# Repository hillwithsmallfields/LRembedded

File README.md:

# LRembedded

Embedded controllers for my Land Rover

I rebuilt and stretched a Land Rover a few years ago, and am starting
to add some microcontrollers.

battery_monitor_charger
=======================

A raspberry pi based system in my garage, connected to the vehicle
batteries by an umbilical, that monitors the voltage and switches a
charger on as needed; also alerts me if the battery connection is lost.

central
=======

An ADK Mega that looks at lots of status lines and communicates with
an Android tablet.

heater
======

Controls some motorized valves directing the output of an air heater.

mc8_tester
==========

A tester for the 8-pin connection system I use for the main wiring,
with connection names built in.

tacho
=====

Scales the output frequency of the alternator tacho connection to
match the requirements of the gauge.

upperwinch
==========

Soft-start controller for a small electric winch.

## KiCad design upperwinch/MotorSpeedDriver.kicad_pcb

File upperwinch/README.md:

MotorSpeedDriver
================

This is an Arduino-based driver for a motor speed controller,
providing ramp-up and ramp-down of speed from two buttons instead of
having to operate switches and a potentiometer.

The motor is a small (900Kgf) winch on my Land Rover roof rack.

The circuit that this combination replaces is an H-bridge of relays
operated by pairs of pushbuttons (on different parts of the vehicle),
one of each pair to run it in each direction.

As the winch is noisy, I wanted to make it possible to vary the speed,
but I wanted to keep the simple two-button interface.

I asked an electronics professional about designing the motor
controller, and he said don't even try at that sort of current (70A),
just buy a ready-made one; too much can go wrong (like switching on
the wrong parts of an H-bridge together).  The unit I bought has a
potentiometer with three connections, and a click-switch on it with
two; and an SPDT switch for selecting the direction.  Both of the
switches are to ground, and work by pulling down.

Hardware
========

For experimentation, I'm using an Arduino Nano; for the final version,
on a PCB, I'll use an ATmega328 directly.

Software
========

Operation
---------

Pressing one button steadily increases the speed in that direction; if
the motor was going in the other direction, it'll slow it down, until
it passes through zero and speeds up in the other direction.

Pressing both buttons at once stops the motor immediately.

Starting
--------

As the buttons are exposed to the elements, although they're nominally
weatherproof, sometimes it takes a few presses to get them to close
the circuit, and as I don't want to risk starting the motor in one
direction then not being able to stop it, the software won't start the
motor until both buttons have been pressed and released.

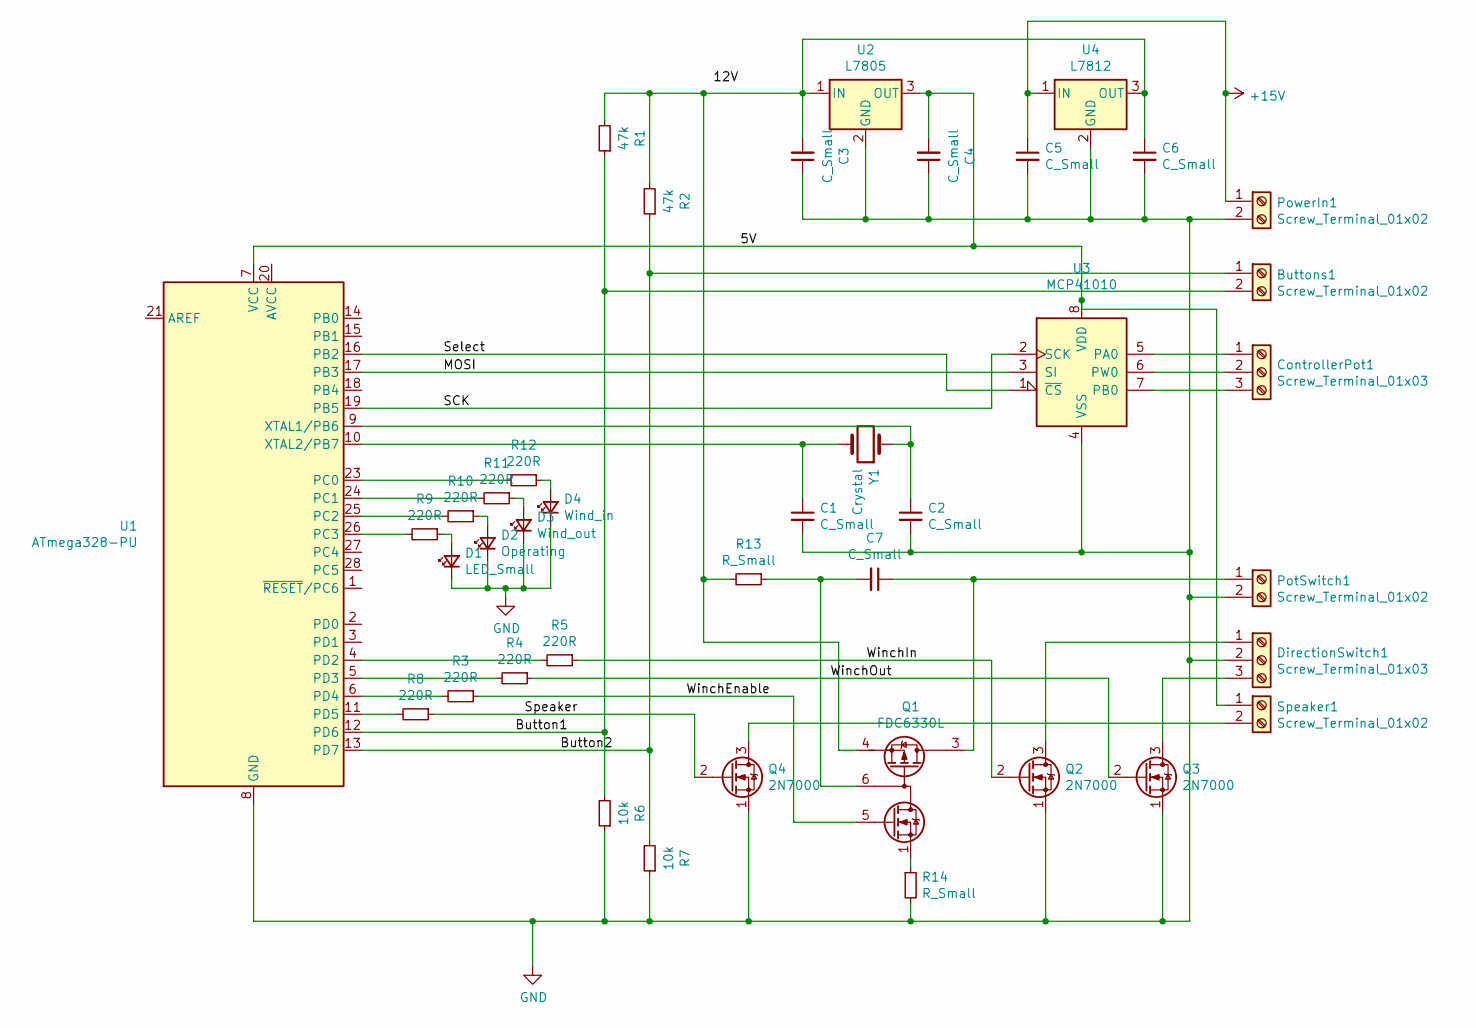
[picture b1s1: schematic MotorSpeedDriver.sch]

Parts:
Buttons1: Screw_Terminal_01x02; TerminalBlock_Phoenix_MKDS-3-2-5.08_1x02_P5.08mm_Horizontal
C1, C2, C3, C4, C5, C6, C7: C_Small; C_Disc_D12.0mm_W4.4mm_P7.75mm
ControllerPot1: Screw_Terminal_01x03; TerminalBlock_Phoenix_MKDS-3-3-5.08_1x03_P5.08mm_Horizontal
D1: LED_Small; LED_D5.0mm
D2: Operating; LED_D5.0mm
D3: Wind_out; LED_D5.0mm
D4: Wind_in; LED_D5.0mm
DirectionSwitch1: Screw_Terminal_01x03; TerminalBlock_Phoenix_MKDS-3-3-5.08_1x03_P5.08mm_Horizontal
PotSwitch1: Screw_Terminal_01x02; TerminalBlock_Phoenix_MKDS-3-2-5.08_1x02_P5.08mm_Horizontal
PowerIn1: Screw_Terminal_01x02; TerminalBlock_Phoenix_MKDS-3-2-5.08_1x02_P5.08mm_Horizontal
Q1: FDC6330L; TSOT-23-6_HandSoldering
Q2, Q3, Q4: 2N7000; TO-92_Inline
R1, R2: 47k; R_Axial_DIN0309_L9.0mm_D3.2mm_P12.70mm_Horizontal
R3, R4, R5, R8, R9, R10, R11, R12: 220R; R_Axial_DIN0309_L9.0mm_D3.2mm_P12.70mm_Horizontal
R6, R7: 10k; R_Axial_DIN0309_L9.0mm_D3.2mm_P12.70mm_Horizontal
R13, R14: R_Small; R_Axial_DIN0309_L9.0mm_D3.2mm_P12.70mm_Horizontal
Speaker1: Screw_Terminal_01x02; TerminalBlock_Phoenix_MKDS-3-2-5.08_1x02_P5.08mm_Horizontal
U1: ATmega328-PU; DIP-28_W7.62mm
U2: L7805; TO-220-3_Vertical
U3: MCP41010; DIP-8_W7.62mm
U4: L7812; TO-220-3_Vertical
Y1: Crystal; Crystal_HC18-U_Horizontal

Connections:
+15V: C5.1, PowerIn1.1, U4.1 (IN)
/5V: C4.2, Speaker1.1, U1.7 (VCC), U2.3 (OUT), U3.8 (VDD)
/Button1: Buttons1.2, R1.1, R6.2, U1.12 (PD6)
/Button2: Buttons1.1, R2.1, R7.2, U1.13 (PD7)
/MOSI: U1.17 (PB3), U3.3 (SI)
/SCK: U1.19 (PB5), U3.2 (SCK)
/Select: U1.16 (PB2), U3.1 (~CS)
/Speaker: Q4.2 (G), R8.1
/WinchEnable: Q1.5 (G1), R3.1
/WinchIn: Q2.2 (G), R5.1
/WinchOut: Q3.2 (G), R4.1
GND: C1.2, C2.2, C3.1, C4.1, C5.2, C6.2, D1.1 (K), D2.1 (K), D3.1 (K), D4.1 (K), DirectionSwitch1.2, PotSwitch1.2, PowerIn1.2, Q2.1 (S), Q3.1 (S), Q4.1 (S), R6.1, R7.1, R14.2, U1.8 (GND), U1.22 (GND), U2.2 (GND), U3.4 (VSS), U4.2 (GND)
unnamed: C1.1, U1.10 (XTAL2/PB7), Y1.2
unnamed: C2.1, U1.9 (XTAL1/PB6), Y1.1
unnamed: C3.2, C6.1, Q1.4 (S2), R1.2, R2.2, R13.2, U2.1 (IN), U4.3 (OUT)
unnamed: C7.1, PotSwitch1.1, Q1.2 (D2), Q1.3 (D2)
unnamed: C7.2, Q1.6 (D1), R13.1
unnamed: ControllerPot1.1, U3.5 (PA0)
unnamed: ControllerPot1.2, U3.6 (PW0)
unnamed: ControllerPot1.3, U3.7 (PB0)
unnamed: D1.2 (A), R9.1
unnamed: D2.2 (A), R10.1
unnamed: D3.2 (A), R11.1
unnamed: D4.2 (A), R12.1
unnamed: DirectionSwitch1.1, Q2.3 (D)
unnamed: DirectionSwitch1.3, Q3.3 (D)
unnamed: Q1.1 (S1), R14.1
unnamed: Q4.3 (D), Speaker1.2
unnamed: R3.2, U1.6 (PD4)
unnamed: R4.2, U1.5 (PD3)
unnamed: R5.2, U1.4 (PD2)
unnamed: R8.2, U1.11 (PD5)
unnamed: R9.2, U1.26 (PC3)
unnamed: R10.2, U1.25 (PC2)
unnamed: R11.2, U1.24 (PC1)
unnamed: R12.2, U1.23 (PC0)

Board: 2 copper layers, 40 parts (1 on the bottom side), 36 nets, no tracks yet.

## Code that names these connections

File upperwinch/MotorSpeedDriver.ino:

#include <SPI.h>

#define WITH_LEDs 1

const int ControllerInPin     = 2;  // PD2 // 4
const int ControllerOutPin    = 3;  // PD3 // 5
const int ControllerEnablePin = 4;  // PD4 // 6

const int SpeakerPin          = 5;  // PD5 // 11

const int ButtonInPin         = 6;  // PD6 // 12
const int ButtonOutPin        = 7;  // PD7 // 13

const int PotCSPin            = 10; // PB2 // 16
// MOSI                       = 11; // PB3 // 17
// MISO                       = 12; // PB4 // 18
// SCK                        = 13; // PB5 // 19

#ifdef WITH_LEDs
const int LedInPin            = A0; // PC0 // 23
const int LedOutPin           = A1; // PC1 // 24
const int LedOperatingPin     = A2; // PC2 // 25
const int LedStartingPin      = A3; // PC4 // 26
#endif

void setup() {
  pinMode(ButtonInPin, INPUT);
  pinMode(ButtonOutPin, INPUT);
  pinMode(PotCSPin, OUTPUT);
  pinMode(ControllerInPin, OUTPUT);
  pinMode(ControllerOutPin, OUTPUT);
  pinMode(ControllerEnablePin, OUTPUT);
  pinMode(SpeakerPin, OUTPUT);
#ifdef WITH_LEDs
  pinMode(LedInPin, OUTPUT);
  pinMode(LedOutPin, OUTPUT);
  pinMode(LedOperatingPin, OUTPUT);
  pinMode(LedStartingPin, OUTPUT);
#endif
  // initialize SPI:
  SPI.begin(); 
#ifdef WITH_LEDs
  digitalWrite(LedStartingPin, HIGH);
  digitalWrite(LedOperatingPin, LOW);
  digitalWrite(LedInPin, LOW);
  digitalWrite(LedOutPin, LOW);
#endif
}

void set_pot(int setting) {
  digitalWrite(PotCSPin, LOW);
  delay(100);
  SPI.transfer(setting);
  delay(100);
  digitalWrite(PotCSPin, HIGH);
}

void set_speed(int speed) {
  if (speed == 0) {
    digitalWrite(ControllerEnablePin, LOW);
    digitalWrite(ControllerInPin, LOW);
    digitalWrite(ControllerOutPin, LOW);
    set_pot(0);
#ifdef WITH_LEDs
    digitalWrite(LedInPin, LOW);
    digitalWrite(LedOutPin, LOW);
#endif
  } else if (speed > 0) {
    digitalWrite(ControllerEnablePin, HIGH);
    digitalWrite(ControllerInPin, HIGH);
    digitalWrite(ControllerOutPin, LOW);
    set_pot(speed);
#ifdef WITH_LEDs
    digitalWrite(LedInPin, HIGH);
    digitalWrite(LedOutPin, LOW);
#endif
  } else {
    digitalWrite(ControllerEnablePin, HIGH);
    digitalWrite(ControllerInPin, LOW);
    digitalWrite(ControllerOutPin, HIGH);
    set_pot(-speed);
#ifdef WITH_LEDs
    digitalWrite(LedInPin, LOW);
    digitalWrite(LedOutPin, HIGH);
#endif
  }
}

/* This indicates whether we are in normal operation; otherwise, we
   are checking both buttons work */
int operating = 0;

/* For checking whether the buttons work */
int in_button_count = 0;
int out_button_count = 0;

/* Remembering previous button states, for debouncing */
int prev_in = 0;
int prev_out = 0;

/* For applying changes to the controller only when needed */
int prev_speed = 0;

/* For remembering when the most recent button activity was */
unsigned long last_press = 0;

/* after this long without button presses, go back to checking the
   buttons work */
#define TIMEOUT 1000 * 60 * 5

/* how frequently to poll the buttons etc */
#define CYCLE_TIME 20
#define SPEED_INCREMENT 1
#define SPEED_MAX 255
#define SPEED_MIN -255

void loop() {
  int in_button = digitalRead(ButtonInPin) == 0;
  int out_button = digitalRead(ButtonOutPin) == 0;
  if (operating) {
    int speed = prev_speed;
    if (in_button && prev_in) {
      if (out_button && prev_out) {
        speed = 0;
      } else {
        if (speed < SPEED_MAX) {
          speed += SPEED_INCREMENT;
        }
      }
    } else if (out_button && prev_out) {
      if (speed > SPEED_MIN) {
        speed -= SPEED_INCREMENT;
      }
    }
    if (speed != prev_speed) {
      set_speed(speed);
    }
    if (prev_in != in_button || prev_out != out_button) {
      last_press = millis();
    } else {
      if (millis() - last_press > TIMEOUT) {
        operating = 0;
#ifdef WITH_LEDs
        digitalWrite(LedOperatingPin, LOW);
        digitalWrite(LedStartingPin, HIGH);
#endif
      }
    }
  } else {
    if (prev_in && ! in_button) {
      in_button_count++;
    }
    if (prev_out && ! out_button) {
      out_button_count++;
    }
    if (in_button_count >= 3 && out_button_count >= 3) {
      operating = 1;
#ifdef WITH_LEDs
      digitalWrite(LedOperatingPin, HIGH);
      digitalWrite(LedStartingPin, LOW);
#endif
    }
  }
  prev_in = in_button;
  prev_out = out_button;
  delay(CYCLE_TIME);
}

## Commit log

2019-10-14 First draft of manifold controller
2019-10-15 Document and tidy a bit more
2019-10-15 Control whether full on is automatic
2019-10-15 More tidying
2019-10-15 Add stubs
2019-10-15 Brief notes
2019-10-21 Switch motor off at end of calibration
2019-10-21 Remove clutch control
    And add some notes.
2019-10-25 Go back to using the clutches
    I had been thinking of gluing them into position, but someone pointed
    out that I may need them to slip a bit at the end of the travel, when
    exploring for the limits.
2019-11-07 Add some notes
2019-11-10 Start sketching
2019-11-12 Add line to switch audio amplifier power
2020-01-16 Start notes and documentation file
2020-01-16 More working notes
2020-01-16 Add description
2020-01-23 edit mechanical notes
2020-01-23 Move file into directory as required by the Arduino IDE
2020-01-23 Get it compiling!
2021-10-10 Move upper winch controller from its own repo
2021-10-10 Move MC8 tester from its own repo
2021-10-10 Add stub for battery monitor and charger program
2021-10-31 Add draft of front panel
2021-10-31 catchup on local changes
2021-10-31 catchup
2021-10-31 add stub for rear panel
2022-03-04 add IEC socket shapes
2022-03-06 shape and position holes in back panel
2022-03-06 adjust front panel hole positions
2022-03-20 Add board mountings
2025-11-23 checkpoint
2025-11-30 add corner holes
2025-11-30 add more ethernet ports
2025-11-30 move LCD panel 2mm left, as marked up
2025-12-20 front panel changes
    Enlarge LCD cutout and move it and the small sockets to make room for
    the meter.
2025-12-20 move holes around, to minimize stress on HDMI socket on RPi
2026-02-09 re-arrange holes in rear panel
    because the internal USB leads wouldn't reach that far from the Pi
    Also added an audio output socket.
2026-02-09 added pushbottons
2026-02-09 remove old contents
2026-02-09 add new mounting board
2026-02-10 Move dimensions to common file
2026-02-10 more coordinate stuff
